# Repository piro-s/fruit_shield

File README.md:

# fruit_shield
26 pin shield for Fruit SBC with logical level matching.
Version 0.1, just test.

## scheme:

## pcb:
### top:

### bottom:

## gerber:
Archive for production:
[gerber](https://github.com/piro-s/fruit_shield/raw/main/gerber/fruit_shield_v0.1_github.zip)

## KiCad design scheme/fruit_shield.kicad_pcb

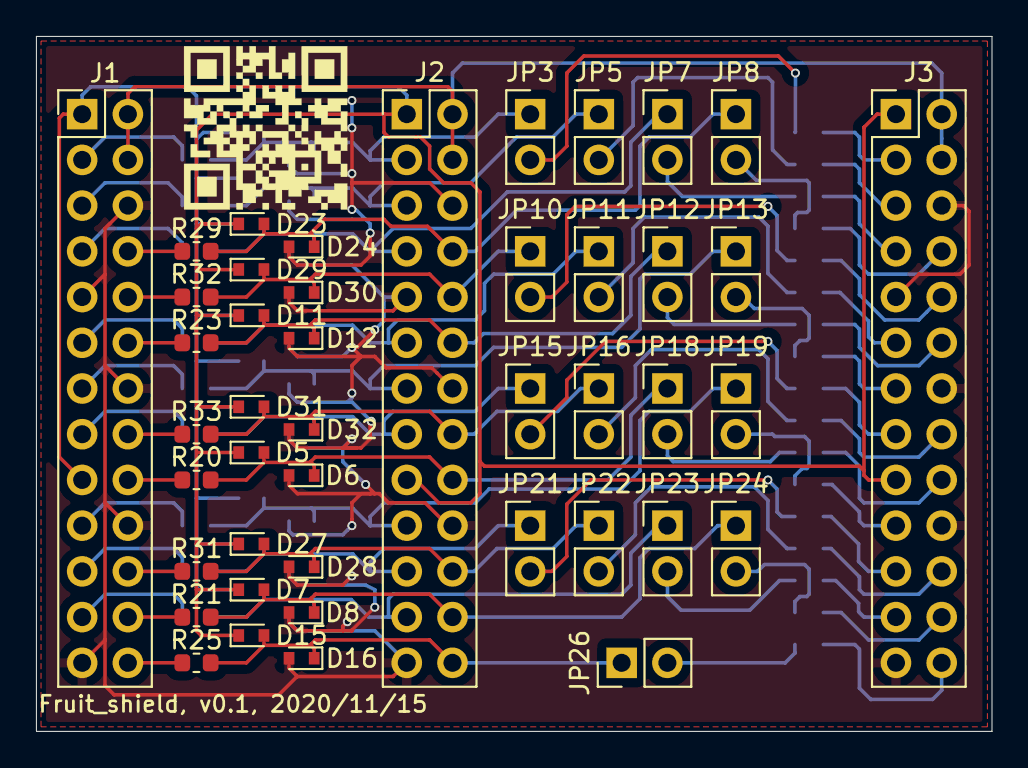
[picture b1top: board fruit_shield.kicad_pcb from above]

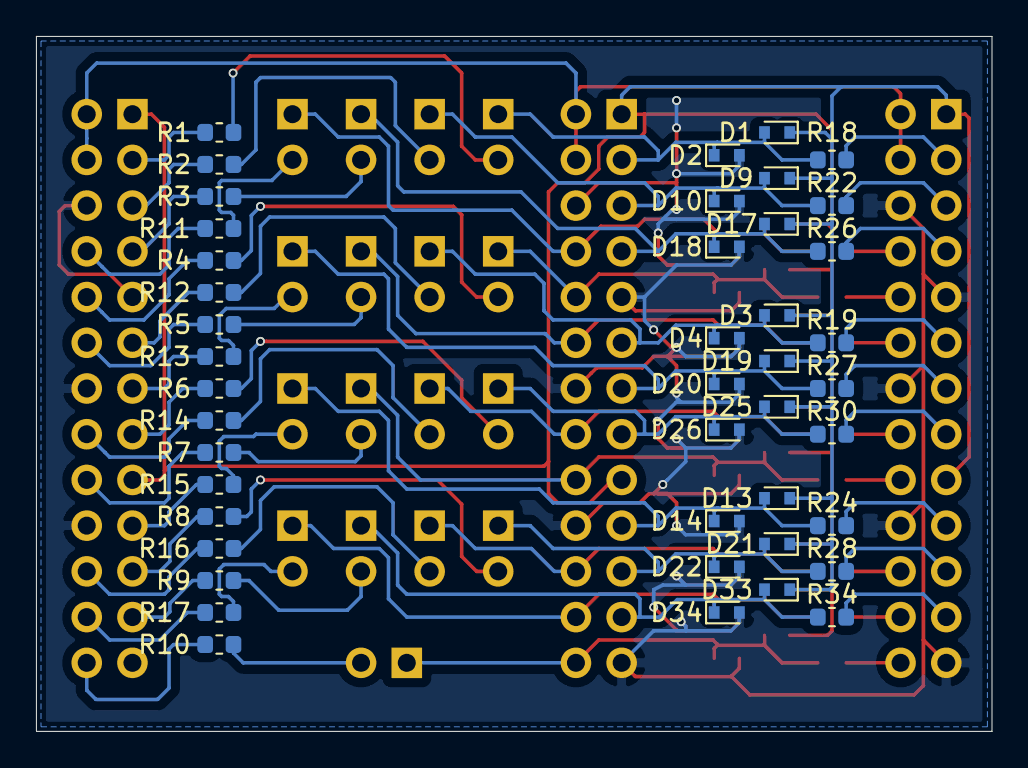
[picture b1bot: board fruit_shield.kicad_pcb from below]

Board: 2 copper layers, 53.1 x 38.6 mm, 88 parts (44 on the bottom side), 71 nets.

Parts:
D1, D2, D3, D4, D5, D6, D7, D8, D9, D10, D11, D12, D13, D14, D15, D16, D17, D18, D19, D20, D21, D22, D23, D24, D25, D26, D27, D28, D29, D30, D31, D32, D33, D34: 1N5819; D_SOD-523
J1: Fruit_Header; PinHeader_2x13_P2.54mm_Vertical
J2: Out; PinHeader_2x13_P2.54mm_Vertical
J3: Out_adj; PinHeader_2x13_P2.54mm_Vertical
JP3, JP5, JP7, JP8, JP10, JP11, JP12, JP13, JP15, JP16, JP18, JP19, JP21, JP22, JP23, JP24, JP26: Jumper_NO_Small; PinHeader_1x02_P2.54mm_Vertical
R1, R2, R3, R4, R5, R6, R7, R8, R9, R10, R11, R12, R13, R14, R15, R16, R17: 2.7k; R_0603_1608Metric
R18, R19, R20, R21, R22, R23, R24, R25, R26, R27, R28, R29, R30, R31, R32, R33, R34: 33; R_0603_1608Metric

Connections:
+3V3: D1.1, D3.1, D5.1, D7.1, D9.1, D11.1, D13.1, D15.1, D17.1, D19.1, D21.1, D23.1, D25.1, D27.1, D29.1, D31.1, D33.1, J1.1, J1.17, J2.1, J2.17, J3.1, J3.17
+5V: J1.2, J1.4, J2.2, J2.4, J3.2, J3.4
/Fruit_3: J1.3, R18.2
/Fruit_5: J1.5, R22.2
/Fruit_7: J1.7, R26.2
/Fruit_8: J1.8, R29.2
/Fruit_10: J1.10, R32.2
/Fruit_11: J1.11, R19.2
/Fruit_12: J1.12, R23.2
/Fruit_13: J1.13, R27.2
/Fruit_15: J1.15, R30.2
/Fruit_16: J1.16, R33.2
/Fruit_18: J1.18, R20.2
/Fruit_19: J1.19, R24.2
/Fruit_21: J1.21, R28.2
/Fruit_22: J1.22, R31.2
/Fruit_23: J1.23, R34.2
/Fruit_24: J1.24, R21.2
/Fruit_26: J1.26, R25.2
/Out_3: D1.2, D2.1, J2.3, JP3.1, R18.1
/Out_5: D9.2, D10.1, J2.5, JP5.1, R22.1
/Out_7: D17.2, D18.1, J2.7, JP7.1, R26.1
/Out_8: D23.2, D24.1, J2.8, JP8.1, R29.1
/Out_10: D29.2, D30.1, J2.10, JP10.1, R32.1
/Out_11: D3.2, D4.1, J2.11, JP11.1, R19.1
/Out_12: D11.2, D12.1, J2.12, JP12.1, R23.1
/Out_13: D19.2, D20.1, J2.13, JP13.1, R27.1
/Out_15: D25.2, D26.1, J2.15, JP15.1, R30.1
/Out_16: D31.2, D32.1, J2.16, JP16.1, R33.1
/Out_18: D5.2, D6.1, J2.18, JP18.1, R20.1
/Out_19: D13.2, D14.1, J2.19, JP19.1, R24.1
/Out_21: D21.2, D22.1, J2.21, JP21.1, R28.1
/Out_22: D27.2, D28.1, J2.22, JP22.1, R31.1
/Out_23: D33.2, D34.1, J2.23, JP23.1, R34.1
/Out_24: D7.2, D8.1, J2.24, JP24.1, R21.1
/Out_26: D15.2, D16.1, J2.26, JP26.1, R25.1
GND: D2.2, D4.2, D6.2, D8.2, D10.2, D12.2, D14.2, D16.2, D18.2, D20.2, D22.2, D24.2, D26.2, D28.2, D30.2, D32.2, D34.2, J1.6, J1.9, J1.14, J1.20, J1.25, J2.6, J2.9, J2.14, J2.20, J2.25, J3.6, J3.9, J3.14, J3.20, J3.25
unnamed: J3.3, R1.1
unnamed: J3.5, R2.1
unnamed: J3.7, R3.1
unnamed: J3.8, R11.1
unnamed: J3.10, R4.1
unnamed: J3.11, R12.1
unnamed: J3.12, R5.1
unnamed: J3.13, R13.1
unnamed: J3.15, R6.1
unnamed: J3.16, R14.1
unnamed: J3.18, R7.1
unnamed: J3.19, R15.1
unnamed: J3.21, R8.1
unnamed: J3.22, R16.1
unnamed: J3.23, R9.1
unnamed: J3.24, R17.1
unnamed: J3.26, R10.1
unnamed: JP3.2, R1.2
unnamed: JP5.2, R2.2
unnamed: JP7.2, R3.2
unnamed: JP8.2, R11.2
unnamed: JP10.2, R4.2
unnamed: JP11.2, R12.2
unnamed: JP12.2, R5.2
unnamed: JP13.2, R13.2
unnamed: JP15.2, R6.2
unnamed: JP16.2, R14.2
unnamed: JP18.2, R7.2
unnamed: JP19.2, R15.2
unnamed: JP21.2, R8.2
unnamed: JP22.2, R16.2
unnamed: JP23.2, R9.2
unnamed: JP24.2, R17.2
unnamed: JP26.2, R10.2

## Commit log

2020-11-15 v0.1
    Test version
2020-11-15 v0.1 readme
    readme.md
2020-11-15 v0.1 readme correct
    correct readme.md
